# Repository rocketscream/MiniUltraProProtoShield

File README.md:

# MiniUltraProProtoShield
A simple proto shield for Mini Ultra Pro board.

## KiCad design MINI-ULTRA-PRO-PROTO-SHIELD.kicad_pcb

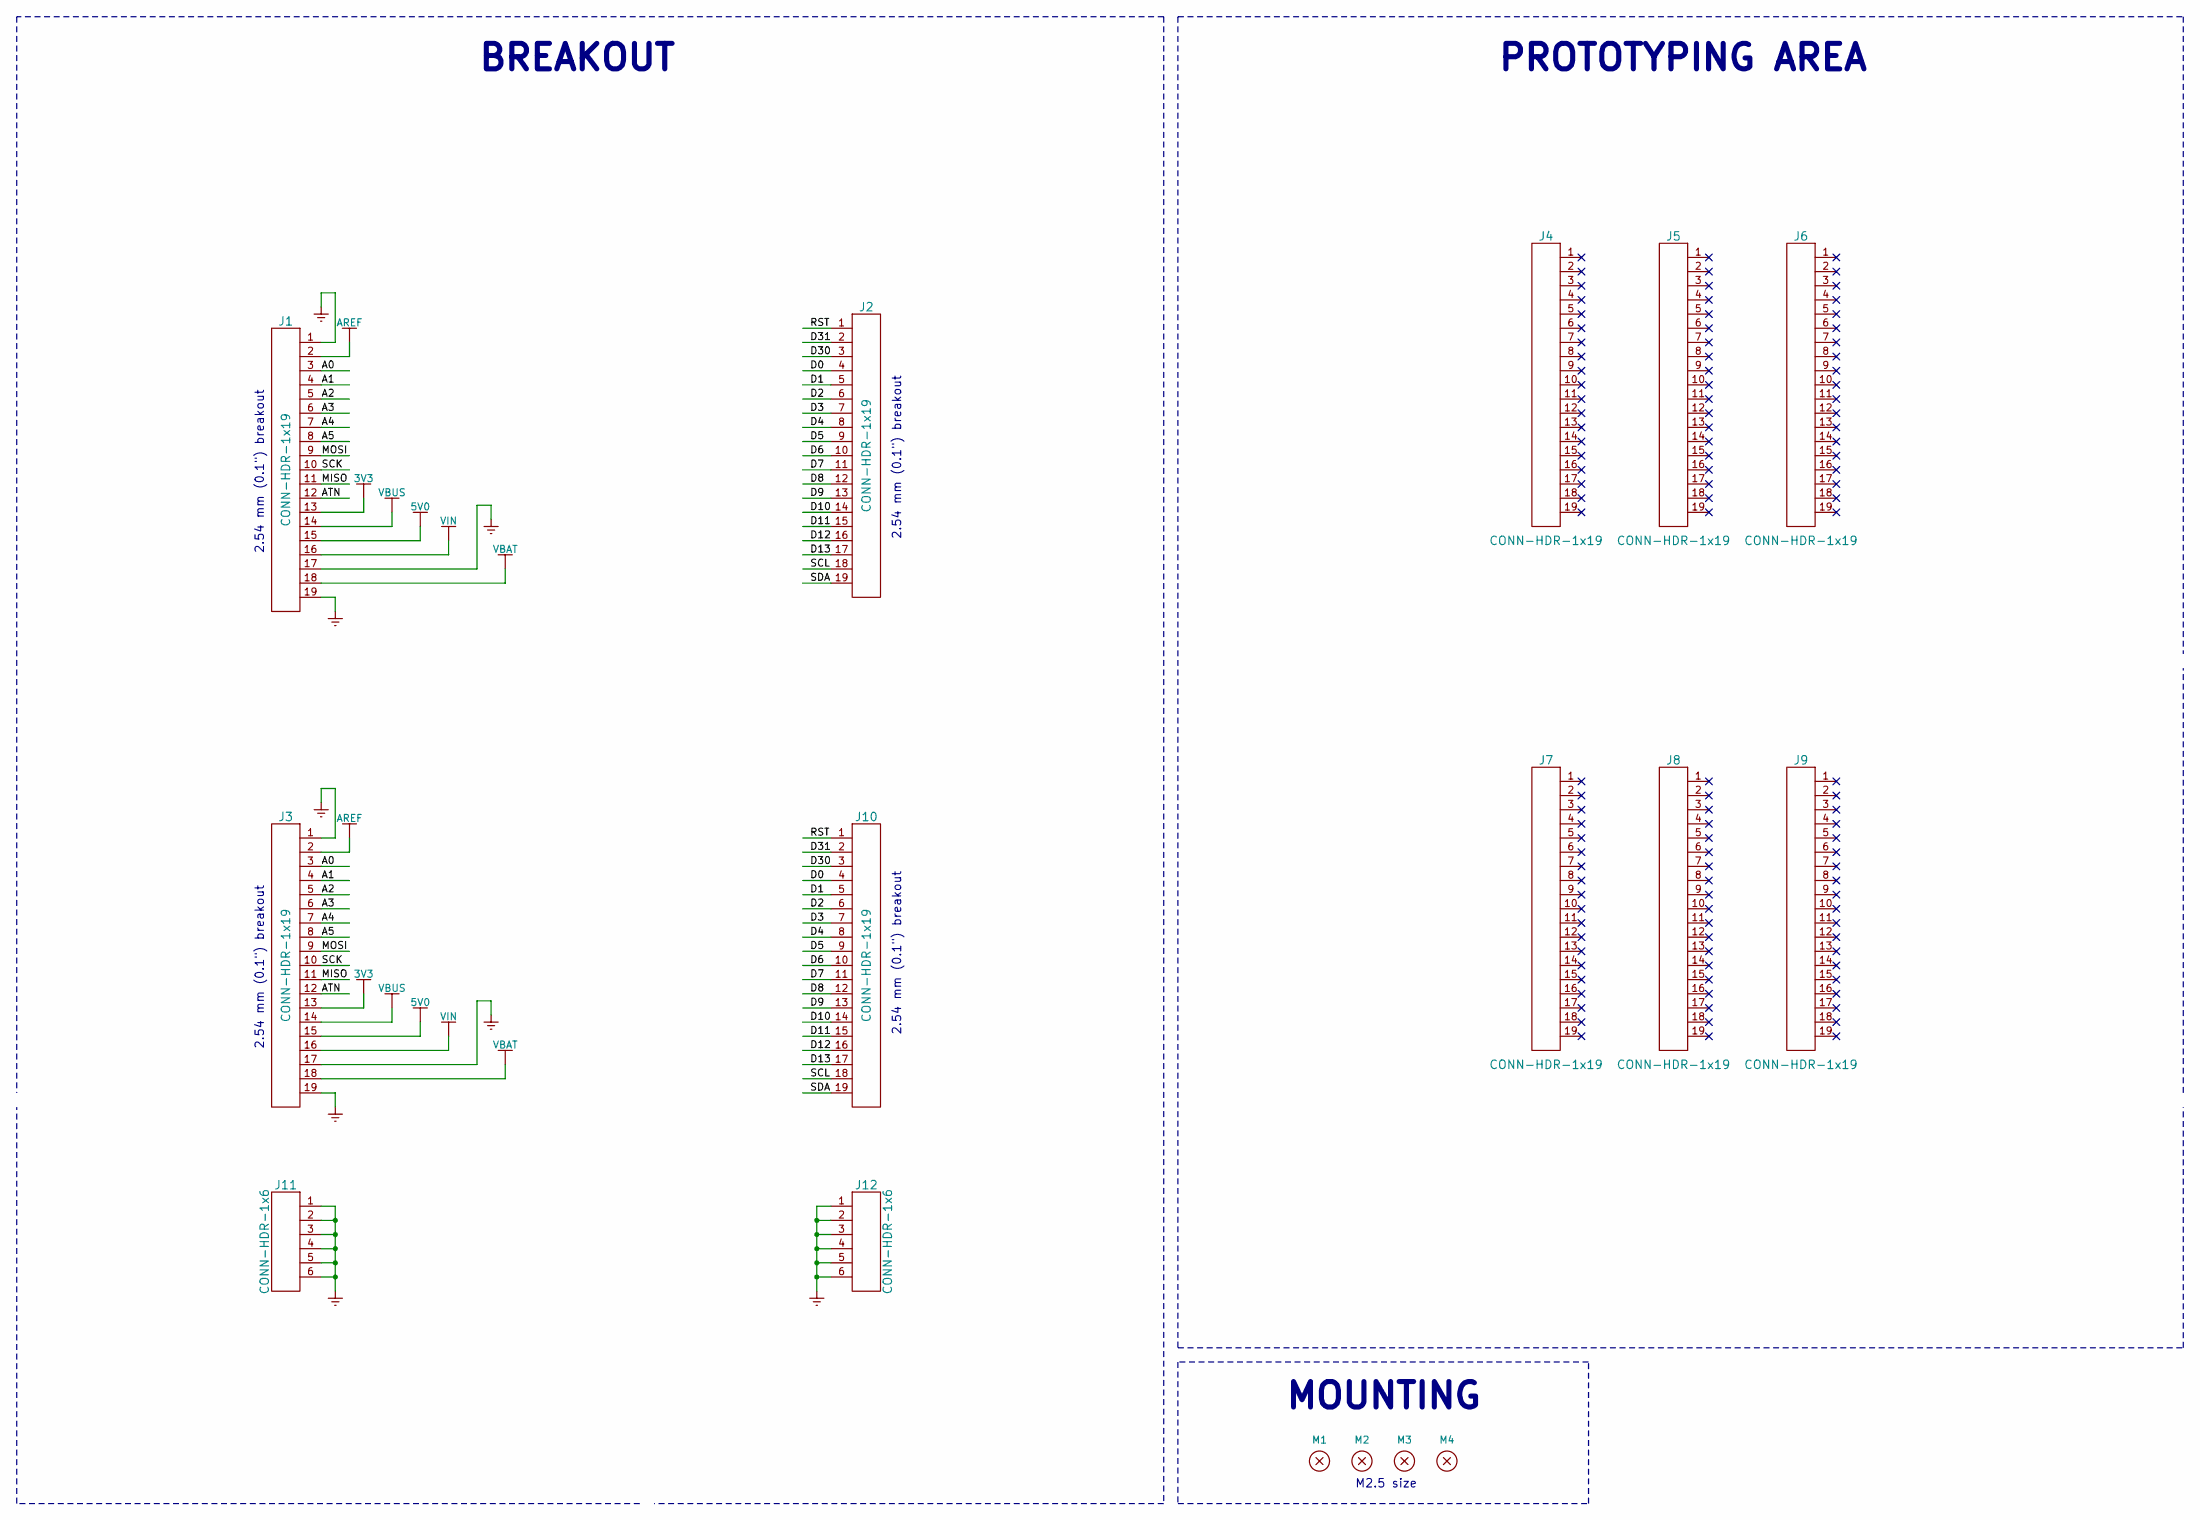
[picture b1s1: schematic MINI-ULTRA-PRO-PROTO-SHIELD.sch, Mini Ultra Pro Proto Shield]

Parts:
J1, J2, J3, J10: CONN-HDR-1x19; HDR_1x19_Pitch2.54mm
J4, J5, J6, J7, J8, J9: CONN-HDR-1x19; HDR_1x19_Pitch2.54mm_WithoutSilk
J11, J12: CONN-HDR-1x6; HDR_1x6_Pitch2.54mm_WithoutSilk
M1, M2, M3, M4: MOUNT_HOLE; HOLE_NPTH_2.2MM

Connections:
3V3: J1.13, J3.13
5V0: J1.15, J3.15
/A0: J1.3, J3.3
/A1: J1.4, J3.4
/A2: J1.5, J3.5
/A3: J1.6, J3.6
/A4: J1.7, J3.7
/A5: J1.8, J3.8
/ATN: J1.12, J3.12
/D0: J2.4, J10.4
/D1: J2.5, J10.5
/D2: J2.6, J10.6
/D3: J2.7, J10.7
/D4: J2.8, J10.8
/D5: J2.9, J10.9
/D6: J2.10, J10.10
/D7: J2.11, J10.11
/D8: J2.12, J10.12
/D9: J2.13, J10.13
/D10: J2.14, J10.14
/D11: J2.15, J10.15
/D12: J2.16, J10.16
/D13: J2.17, J10.17
/D30: J2.3, J10.3
/D31: J2.2, J10.2
/MISO: J1.11, J3.11
/MOSI: J1.9, J3.9
/RST: J2.1, J10.1
/SCK: J1.10, J3.10
/SCL: J2.18, J10.18
/SDA: J2.19, J10.19
AREF: J1.2, J3.2
GND: J1.1, J1.17, J1.19, J3.1, J3.17, J3.19, J11.1, J11.2, J11.3, J11.4, J11.5, J11.6, J12.1, J12.2, J12.3, J12.4, J12.5, J12.6
VBAT: J1.18, J3.18
VBUS: J1.14, J3.14
VIN: J1.16, J3.16

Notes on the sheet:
MOUNTING
BREAKOUT
M2.5 size
2.54 mm (0.1") breakout
PROTOTYPING AREA

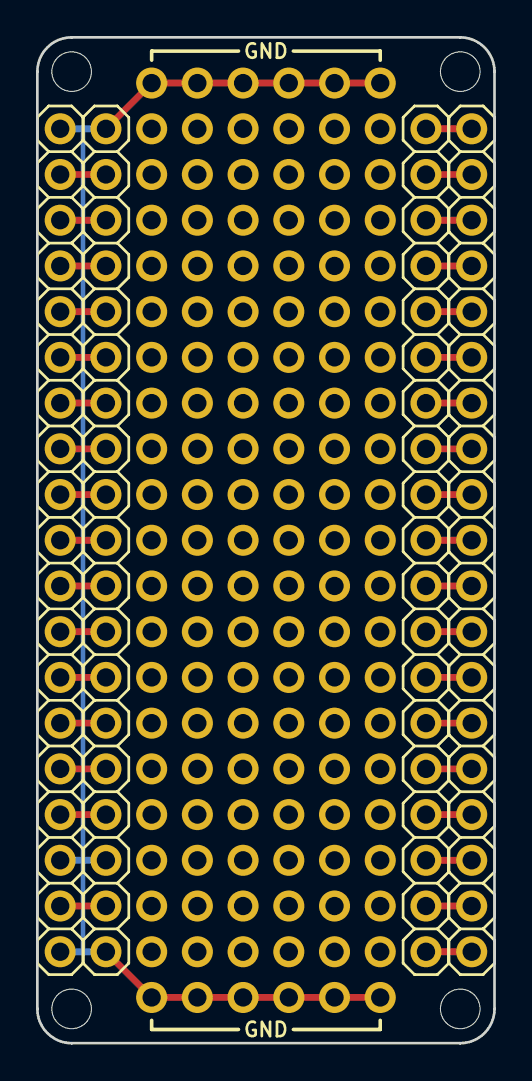
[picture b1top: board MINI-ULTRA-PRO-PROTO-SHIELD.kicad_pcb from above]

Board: 2 copper layers, 25.4 x 55.9 mm, 16 parts (0 on the bottom side), 36 nets.

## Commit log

2016-02-23 Initial public release v0.10
2016-02-23 Initial public release for version 0.10.
